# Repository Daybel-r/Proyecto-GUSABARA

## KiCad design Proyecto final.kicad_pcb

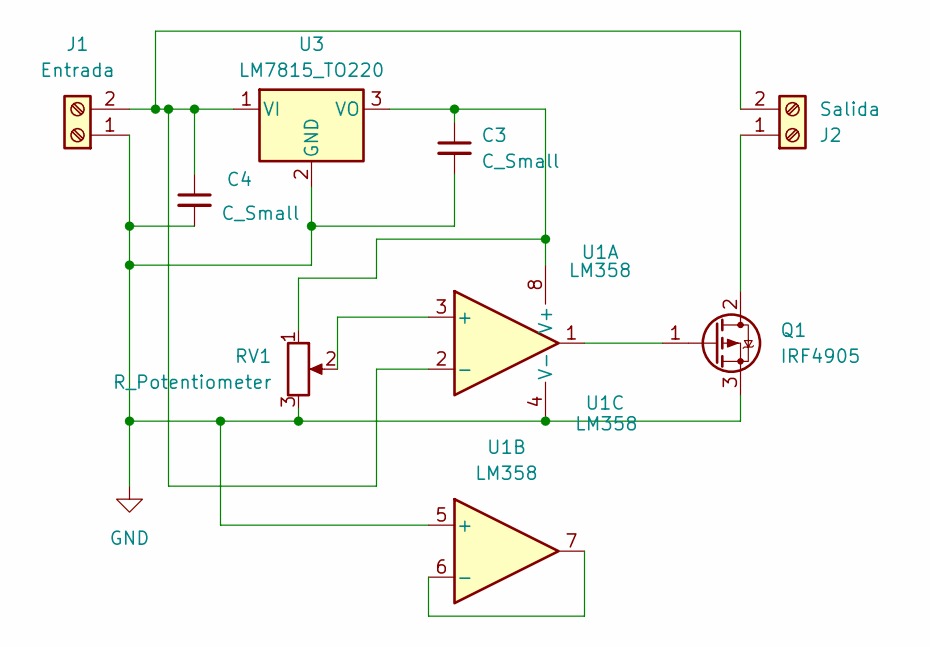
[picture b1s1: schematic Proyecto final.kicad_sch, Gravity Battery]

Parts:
C3, C4: C_Small; C_Disc_D5.0mm_W2.5mm_P2.50mm
J1: Entrada; TerminalBlock_Phoenix_MKDS-1,5-2_1x02_P5.00mm_Horizontal
J2: Salida; TerminalBlock_Phoenix_MKDS-1,5-2_1x02_P5.00mm_Horizontal
Q1: IRF4905; TO-220-3_Vertical
RV1: R_Potentiometer; Potentiometer_Bourns_3296W_Vertical
U1: LM358; DIP-8_W7.62mm
U3: LM7815_TO220; TO-220-3_Vertical

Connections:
GND: C3.2, C4.2, J1.1, Q1.3 (S), RV1.3, U1.4 (V-), U1.5 (+), U3.2 (GND)
unnamed: C4.1, J1.2, J2.2, U1.2 (-), U3.1 (VI)
unnamed: J2.1, Q1.2 (D)
unnamed: Q1.1 (G), U1.1
unnamed: RV1.2, U1.3 (+)
unnamed: U1.6 (-), U1.7
unnamed: C3.1, RV1.1, U1.8 (V+), U3.3 (VO)

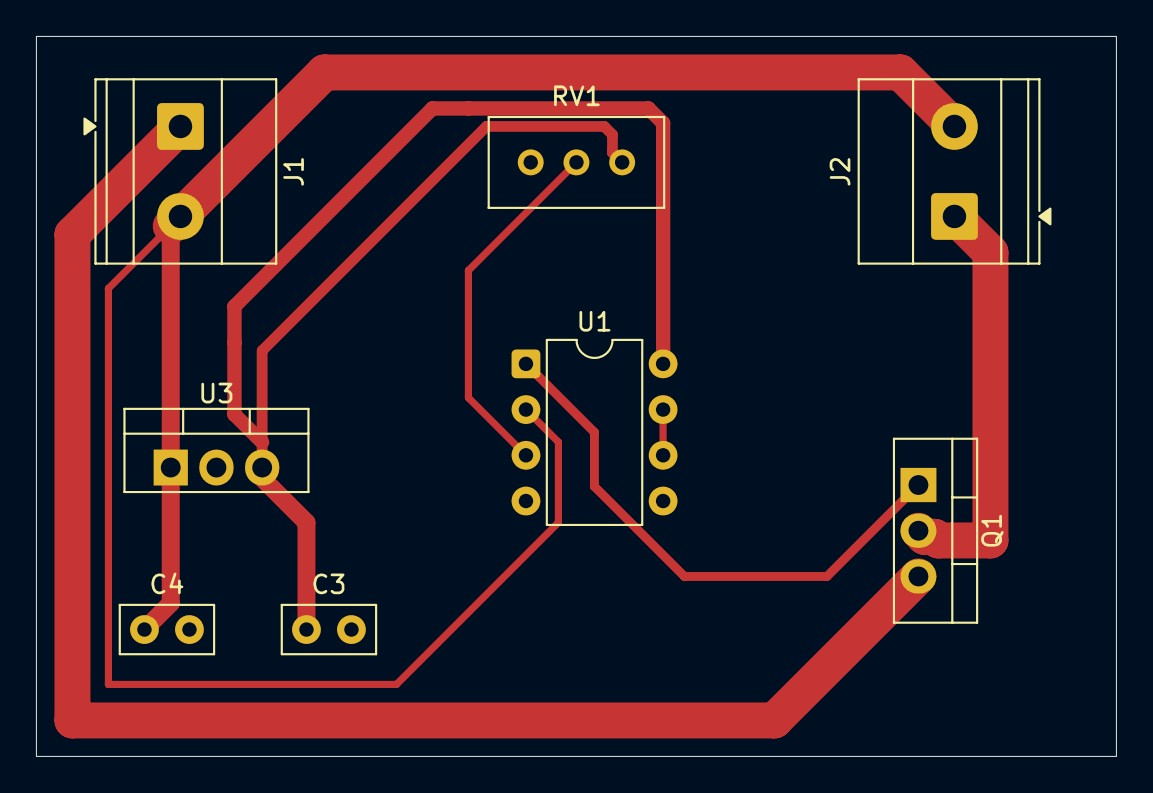
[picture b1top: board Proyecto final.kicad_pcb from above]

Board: 2 copper layers, 60.0 x 40.0 mm, 8 parts (0 on the bottom side), 7 nets.
